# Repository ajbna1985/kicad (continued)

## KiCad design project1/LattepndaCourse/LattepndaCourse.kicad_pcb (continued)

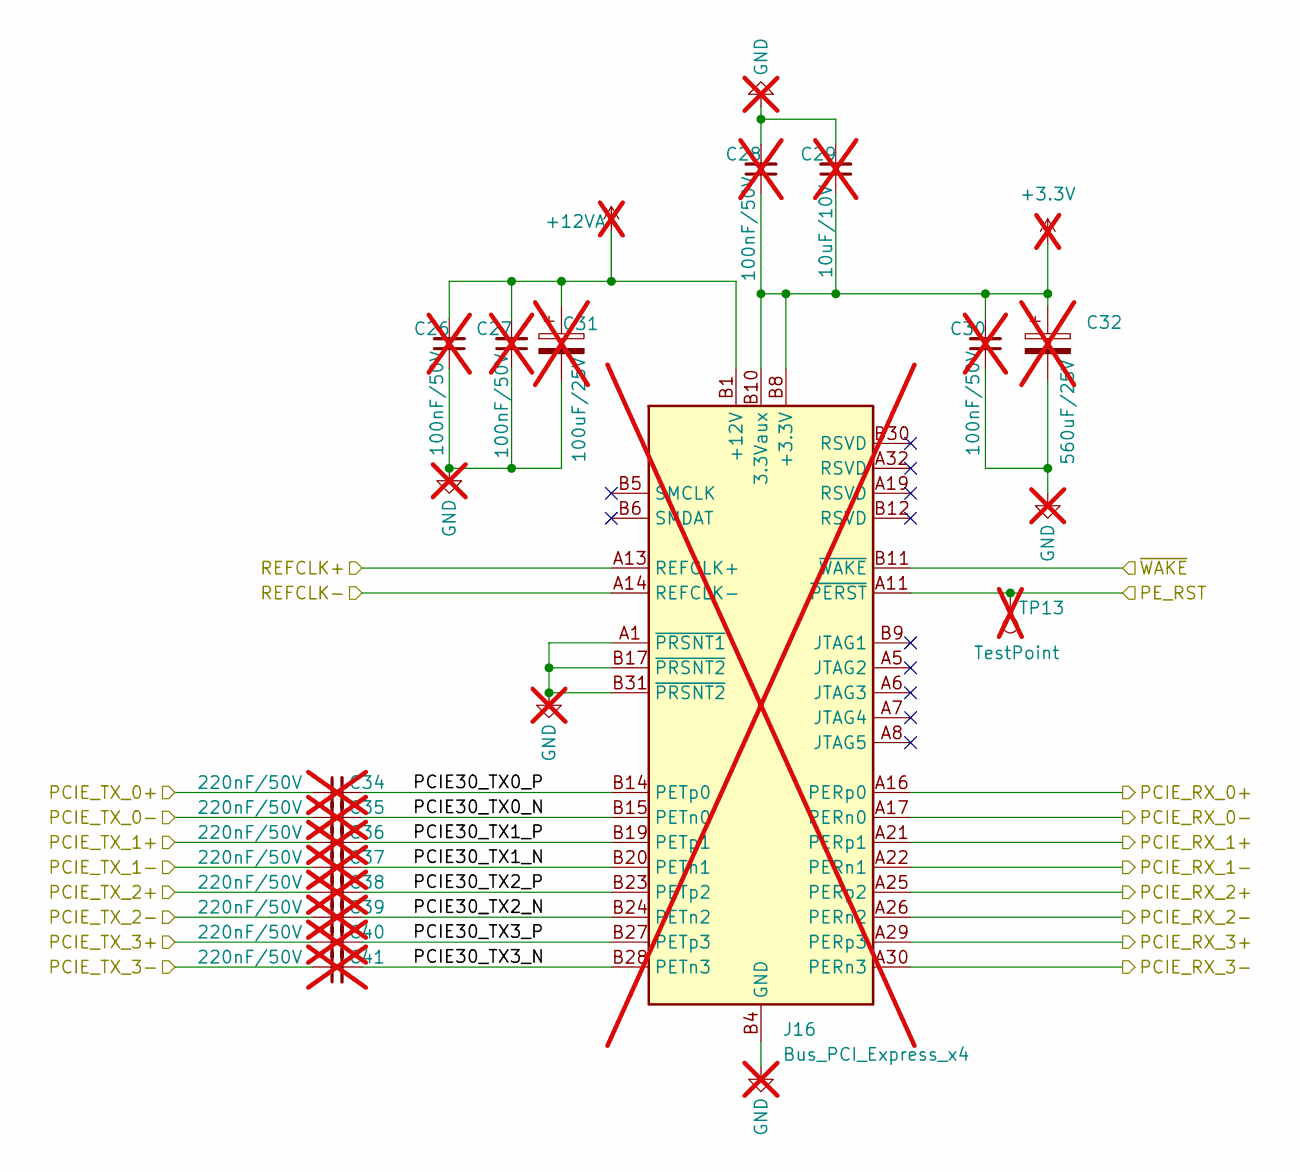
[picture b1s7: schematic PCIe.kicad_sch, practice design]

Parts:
C26, C27, C28, C30: 100nF/50V; C_0603_1608Metric; not fitted
C29: 10uF/10V; C_0603_1608Metric; not fitted
C31: 100uF/25V; CP_Elec_6.3x7.7; not fitted
C32: 560uF/25V; CP_Elec_6.3x7.7; not fitted
C34, C35, C36, C37, C38, C39, C40, C41: 220nF/50V; C_0402_1005Metric; not fitted
J16: Bus_PCI_Express_x4; PCIe_x4_Gen3Slot_Connectors; not fitted
TP13: TestPoint; TestPoint_Pad_D1.5mm; not fitted

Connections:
+3.3V: C28.1, C29.1, C30.2, C32.1, J16.A9 (+3.3V), J16.A10 (+3.3V), J16.B8 (+3.3V), J16.B10 (3.3Vaux); also elsewhere on the board
+5V: C26.1, C27.1, C28.2, C29.2, C30.1, C31.2, C32.2, J16.A1 (~PRSNT1), J16.A4 (GND), J16.A12 (GND), J16.A15 (GND), J16.A18 (GND), J16.A20 (GND), J16.A23 (GND), J16.A24 (GND), J16.A27 (GND), J16.A28 (GND), J16.A31 (GND), J16.B4 (GND), J16.B7 (GND), J16.B13 (GND), J16.B16 (GND), J16.B17 (~PRSNT2), J16.B18 (GND), J16.B21 (GND), J16.B22 (GND), J16.B25 (GND), J16.B26 (GND), J16.B29 (GND), J16.B31 (~PRSNT2), J16.B32 (GND); also elsewhere on the board
+12VA: C26.2, C27.2, C31.1, J16.A2 (+12V), J16.A3 (+12V), J16.B1 (+12V), J16.B2 (+12V), J16.B3 (+12V)
/LaPanda Module/HSIO_8_RX+: C34.1; also elsewhere on the board
/LaPanda Module/HSIO_8_RX-: C35.1; also elsewhere on the board
/LaPanda Module/HSIO_8_TX+: J16.A16 (PERp0); also elsewhere on the board
/LaPanda Module/HSIO_8_TX-: J16.A17 (PERn0); also elsewhere on the board
/LaPanda Module/HSIO_9_RX+: C36.1; also elsewhere on the board
/LaPanda Module/HSIO_9_RX-: C37.1; also elsewhere on the board
/LaPanda Module/HSIO_9_TX+: J16.A21 (PERp1); also elsewhere on the board
/LaPanda Module/HSIO_9_TX-: J16.A22 (PERn1); also elsewhere on the board
/LaPanda Module/HSIO_10_RX+: J16.A25 (PERp2); also elsewhere on the board
/LaPanda Module/HSIO_10_RX-: J16.A26 (PERn2); also elsewhere on the board
/LaPanda Module/HSIO_10_TX+: C38.1; also elsewhere on the board
/LaPanda Module/HSIO_10_TX-: C39.1; also elsewhere on the board
/LaPanda Module/HSIO_11_RX+: J16.A29 (PERp3); also elsewhere on the board
/LaPanda Module/HSIO_11_RX-: J16.A30 (PERn3); also elsewhere on the board
/LaPanda Module/HSIO_11_TX+: C40.1; also elsewhere on the board
/LaPanda Module/HSIO_11_TX-: C41.1; also elsewhere on the board
/LaPanda Module/REFCLK2+: J16.A13 (REFCLK+); also elsewhere on the board
/LaPanda Module/REFCLK2-: J16.A14 (REFCLK-); also elsewhere on the board
/PCIe/PCIE30_TX0_N: C35.2, J16.B15 (PETn0)
/PCIe/PCIE30_TX0_P: C34.2, J16.B14 (PETp0)
/PCIe/PCIE30_TX1_N: C37.2, J16.B20 (PETn1)
/PCIe/PCIE30_TX1_P: C36.2, J16.B19 (PETp1)
/PCIe/PCIE30_TX2_N: C39.2, J16.B24 (PETn2)
/PCIe/PCIE30_TX2_P: C38.2, J16.B23 (PETp2)
/PCIe/PCIE30_TX3_N: C41.2, J16.B28 (PETn3)
/PCIe/PCIE30_TX3_P: C40.2, J16.B27 (PETp3)
/~PLTRST: J16.A11 (~PERST), TP13.1 (1_1); also elsewhere on the board
/~WAKE: J16.B11 (~WAKE); also elsewhere on the board

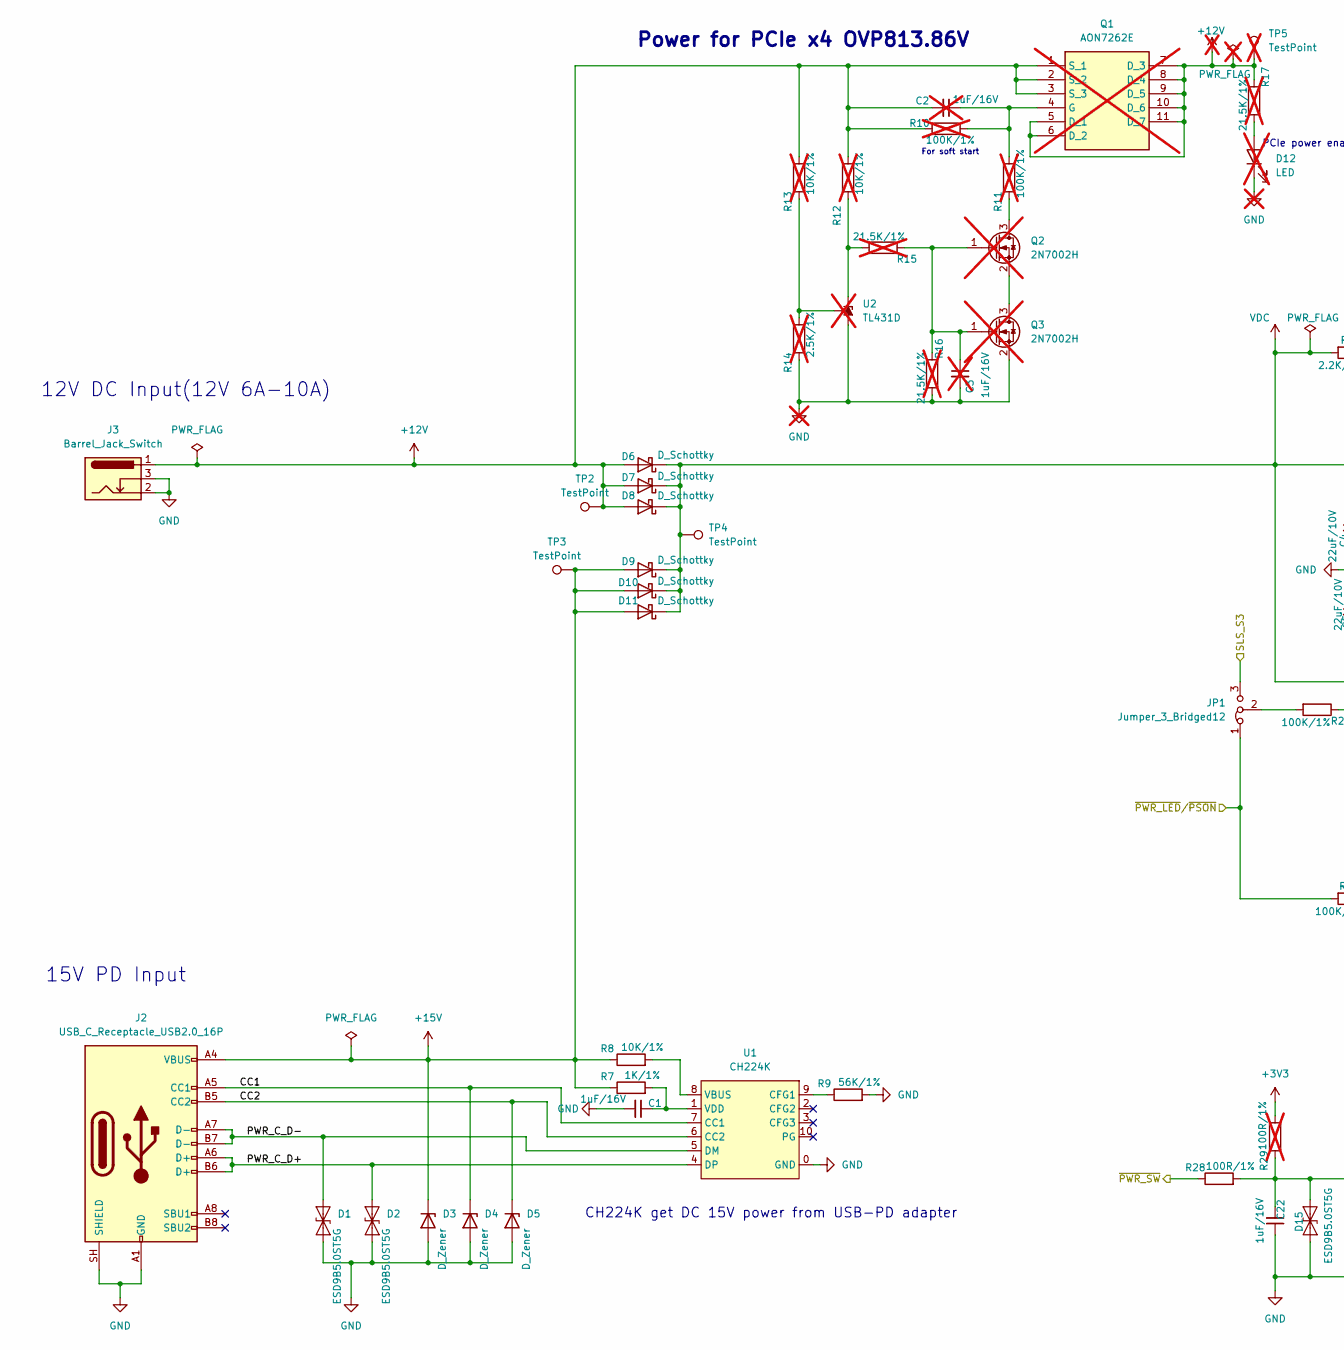
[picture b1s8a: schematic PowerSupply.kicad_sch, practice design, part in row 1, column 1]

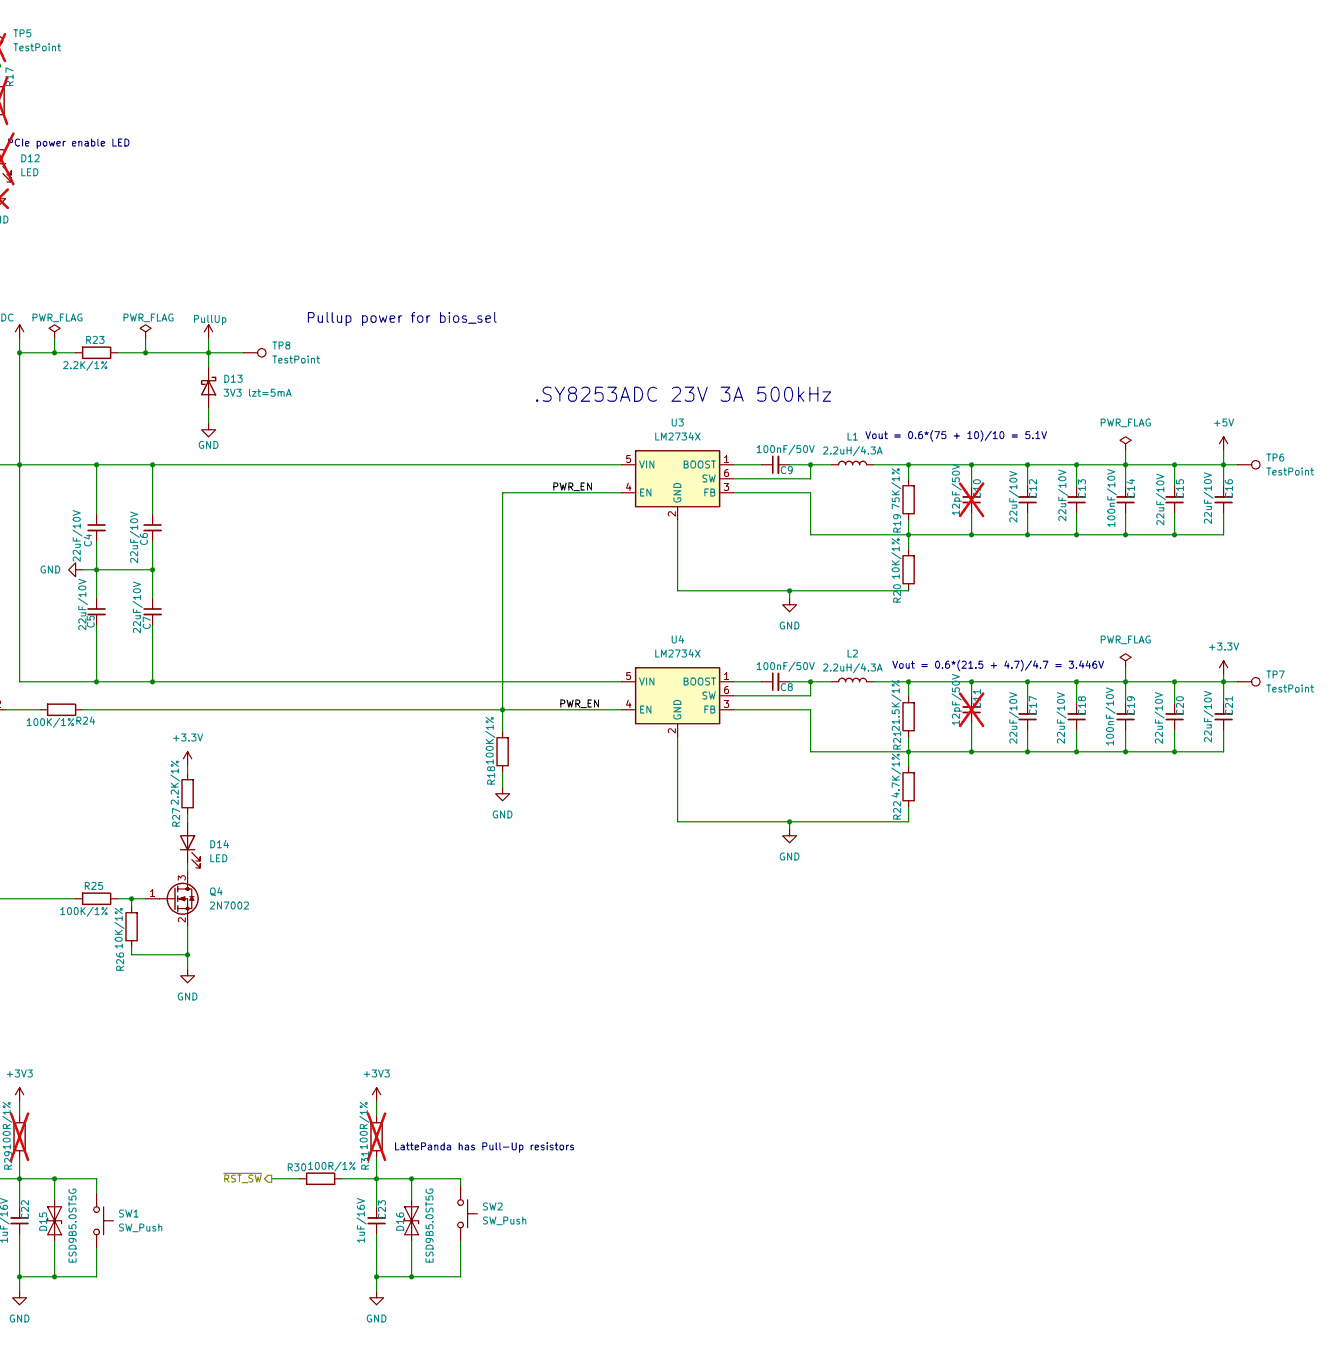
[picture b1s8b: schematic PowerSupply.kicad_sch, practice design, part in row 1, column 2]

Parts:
C1, C22, C23: 1uF/16V; C_0402_1005Metric
C2, C3: 1uF/16V; C_0402_1005Metric; not fitted
C4, C5, C6, C7, C12, C13, C15, C16, C17, C18, C20, C21: 22uF/10V; C_0603_1608Metric
C8, C9: 100nF/50V; C_0603_1608Metric
C10, C11: 12pF/50V; C_0603_1608Metric; not fitted
C14, C19: 100nF/10V; C_0603_1608Metric
D1, D2, D15, D16: ESD9B5.0ST5G; D_0402_1005Metric
D3, D4, D5: D_Zener; D_0402_1005Metric
D6, D7, D8, D9, D10, D11: D_Schottky; D_SMA
D12: LED; LED_0603_1608Metric; not fitted
D13: 3V3 lzt=5mA; D_SOD-323
D14: LED; LED_0603_1608Metric
J2: USB_C_Receptacle_USB2.0_16P; USB_C_Receptacle_G-Switch_GT-USB-7010ASV
J3: Barrel_Jack_Switch; DC_Jack_DC007B_30V_10A
JP1: Jumper_3_Bridged12; PinHeader_1x03_P2.54mm_Vertical
L1, L2: 2.2uH/4.3A; L_Sunlord_SWPA4020S
Q1: AON7262E; MOSFET_PDFN8_3.3x3.3; not fitted
Q2, Q3: 2N7002H; SOT-23; not fitted
Q4: 2N7002; SOT-23
R7: 1K/1%; R_0402_1005Metric
R8, R20, R26: 10K/1%; R_0402_1005Metric
R9: 56K/1%; R_0402_1005Metric
R10, R11: 100K/1%; R_0402_1005Metric; not fitted
R12, R13: 10K/1%; R_0402_1005Metric; not fitted
R14: 2.5K/1%; R_0402_1005Metric; not fitted
R15, R16, R17: 21.5K/1%; R_0402_1005Metric; not fitted
R18, R24, R25: 100K/1%; R_0402_1005Metric
R19: 75K/1%; R_0402_1005Metric
R21: 21.5K/1%; R_0402_1005Metric
R22: 4.7K/1%; R_0402_1005Metric
R23, R27: 2.2K/1%; R_0402_1005Metric
R28, R30: 100R/1%; R_0402_1005Metric
R29, R31: 100R/1%; R_0402_1005Metric; not fitted
SW1, SW2: SW_Push; SW_Push_6x6x6
TP2, TP3, TP4, TP6, TP7, TP8: TestPoint; TestPoint_Pad_D1.5mm
TP5: TestPoint; TestPoint_Pad_D1.5mm; not fitted
U1: USB PD等快充协议受电芯片-CH224K-ESSOP10; ESSOP-10-1EP_3.9x5mm_P1.0mm_EP3.2x2.3
U2: TL431D; SOT-23; not fitted
U3, U4: LM2734X; TSOT-23-6

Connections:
+3.3V: C11.2, C17.2, C18.2, C19.2, C20.2, C21.2, L2.2, R21.2, R27.2, TP7.1 (1_1); also elsewhere on the board
+3V3: R29.2, R31.2; also elsewhere on the board
+5V: C1.2, C3.2, C4.2, C5.1, C6.2, C7.1, C10.2, C12.2, C13.2, C14.2, C15.2, C16.2, C22.1, C23.1, D1.1 (A1), D2.1 (A1), D3.2 (A), D4.2 (A), D5.2 (A), D12.1 (K), D13.2 (A), D15.2 (A2), D16.2 (A2), J2.A1 (GND), J2.A12 (GND), J2.B1 (GND), J2.B12 (GND), J2.SH (SHIELD), J3.2, J3.3, L1.2, Q3.2 (S), Q4.2 (S), R9.2, R14.1, R16.2, R18.1, R19.2, R20.1, R22.1, R26.1, SW1.2, SW2.2, TP6.1 (1_1), U1.0 (GND), U2.2 (A), U2.3 (A), U2.6 (A), U2.7 (A), U3.2 (GND), U4.2 (GND); also elsewhere on the board
+12V: C2.2, D6.2 (A), D7.2 (A), D8.2 (A), J3.1, Q1.1 (S_1), Q1.2 (S_2), Q1.3 (S_3), Q1.5 (D_1), Q1.6 (D_2), Q1.7 (D_3), Q1.8 (D_4), Q1.9 (D_5), Q1.10 (D_6), Q1.11 (D_7), R10.1, R12.2, R13.2, R17.1, TP2.1 (1_1), TP5.1 (1_1); also elsewhere on the board
+15V: D3.1 (K), D9.2 (A), D10.2 (A), D11.2 (A), J2.A4 (VBUS), J2.A9 (VBUS), J2.B4 (VBUS), J2.B9 (VBUS), R7.1, R8.1, TP3.1 (1_1)
/LaPanda Module/SLS_S3: JP1.3 (B); also elsewhere on the board
/LaPanda Module/~RST_SW: R30.1; also elsewhere on the board
/PowerSupply/CC1: D4.1 (K), J2.A5 (CC1), U1.7 (CC1)
/PowerSupply/CC2: D5.1 (K), J2.B5 (CC2), U1.6 (CC2)
/PowerSupply/PWR_C_D+: D2.2 (A2), J2.A6 (D+), J2.B6 (D+), U1.4 (DP)
/PowerSupply/PWR_C_D-: D1.2 (A2), J2.A7 (D-), J2.B7 (D-), U1.5 (DM)
/PowerSupply/PWR_EN: R18.2, R24.1, U3.4 (EN), U4.4 (EN)
/~PWR_LED/~PSON: JP1.1 (A), R25.2; also elsewhere on the board
/~PWR_SW: R28.1; also elsewhere on the board
unnamed: D12.2 (A), R17.2
unnamed: D14.2 (A), R27.1
unnamed: D14.1 (K), Q4.3 (D)
unnamed: C22.2, D15.1 (A1), R28.2, R29.1, SW1.1
unnamed: C23.2, D16.1 (A1), R30.2, R31.1, SW2.1
unnamed: JP1.2 (C), R24.2
unnamed: C2.1, Q1.4 (G), R10.2, R11.2
unnamed: Q2.3 (D), R11.1
unnamed: C3.1, Q2.1 (G), Q3.1 (G), R15.1, R16.1
unnamed: Q2.2 (S), Q3.3 (D)
unnamed: Q4.1 (G), R25.1, R26.2
unnamed: R9.1, U1.9 (CFG1)
unnamed: R8.2, U1.8 (VBUS)
unnamed: C1.1, R7.2, U1.1 (VDD)
unnamed: R12.1, R15.2, U2.1 (K)
unnamed: R13.1, R14.2, U2.8 (REF)
unnamed: C9.1, U3.1 (BOOST)
unnamed: C10.1, C12.1, C13.1, C14.1, C15.1, C16.1, R19.1, R20.2, U3.3 (FB)
unnamed: C9.2, L1.1, U3.6 (SW)
unnamed: C8.1, U4.1 (BOOST)
unnamed: C11.1, C17.1, C18.1, C19.1, C20.1, C21.1, R21.1, R22.2, U4.3 (FB)
unnamed: C8.2, L2.1, U4.6 (SW)
PullUp: D13.1 (K), R23.1, TP8.1 (1_1); also elsewhere on the board
VDC: C4.1, C5.2, C6.1, C7.2, D6.1 (K), D7.1 (K), D8.1 (K), D9.1 (K), D10.1 (K), D11.1 (K), R23.2, TP4.1 (1_1), U3.5 (VIN), U4.5 (VIN); also elsewhere on the board

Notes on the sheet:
CH224K get DC 15V power from USB-PD adapter
For soft start
15V PD Input
Vout = 0.6*(75 + 10)/10 = 5.1V
Power for PCIe x4 OVP813.86V
PCIe power enable LED
Vout = 0.6*(21.5 + 4.7)/4.7 = 3.446V
LattePanda has Pull-Up resistors
.SY8253ADC 23V 3A 500kHz
Pullup power for bios_sel
12V DC Input(12V 6A-10A)

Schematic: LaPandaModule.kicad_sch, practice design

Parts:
A1: LattePanda_Mu; LattePanda_Module_H8.0mm_Horizontal
BT1: Battery_Cell; Battery_Holder_CR1220_S8411-45R
H7, H8: MountingHole_Pad; MountingHole_3mm_M2_Pad_TopOnly
J1: Conn_01x03_Pin; PinHeader_1x03_P2.54mm_Vertical
R1, R2, R3: 10K/1%; R_0402_1005Metric
R4, R5: 100K/1%; R_0402_1005Metric
R6: 1K/1%; R_0402_1005Metric
TP1: TestPoint; TestPoint_Pad_D1.5mm

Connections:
+5V: A1.11 (GND), A1.14 (GND), A1.17 (GND), A1.20 (GND), A1.23 (GND), A1.26 (GND), A1.29 (GND), A1.32 (GND), A1.35 (GND), A1.38 (GND), A1.41 (GND), A1.44 (GND), A1.47 (GND), A1.50 (GND), A1.53 (GND), A1.56 (GND), A1.59 (GND), A1.62 (GND), A1.65 (GND), A1.68 (GND), A1.71 (GND), A1.74 (GND), A1.77 (GND), A1.80 (GND), A1.83 (GND), A1.86 (GND), A1.89 (GND), A1.92 (GND), A1.95 (GND), A1.98 (GND), A1.101 (GND), A1.107 (GND), A1.110 (GND), A1.113 (GND), A1.116 (GND), A1.135 (GND), A1.136 (GND), A1.151 (GND), A1.158 (GND), A1.167 (GND), A1.170 (GND), A1.181 (GND), A1.182 (GND), A1.188 (GND), A1.189 (GND), A1.194 (GND), A1.195 (GND), A1.200 (GND), A1.201 (GND), A1.206 (GND), A1.207 (GND), A1.212 (GND), A1.213 (GND), A1.218 (GND), A1.219 (GND), A1.224 (GND), A1.225 (GND), A1.230 (GND), A1.231 (GND), A1.236 (GND), A1.237 (GND), A1.242 (GND), A1.243 (GND), A1.248 (GND), A1.249 (GND), A1.MP (Mountinge_Pads), BT1.2 (-), H7.1 (1_1), H8.1 (1_1), J1.3, R2.1, R3.1, R4.2, R5.2; also elsewhere on the board
+BATT: A1.115 (VBAT), R6.2
/Fan/FAN_1_PWM: A1.2 (FAN1_PWM); also elsewhere on the board
/Fan/FAN_1_TAC: A1.4 (FAN1_TAC); also elsewhere on the board
/Fan/FAN_2_PWM: A1.6 (FAN2_PWM); also elsewhere on the board
/Fan/FAN_2_TAC: A1.8 (FAN2_TAC); also elsewhere on the board
/Fan/TEMP: A1.9 (TSENSE); also elsewhere on the board
/GPIO/GPP_D0: A1.128 (GPP_D0); also elsewhere on the board
/GPIO/GPP_D1: A1.130 (GPP_D1); also elsewhere on the board
/GPIO/GPP_D2: A1.132 (GPP_D2); also elsewhere on the board
/GPIO/GPP_D3: A1.134 (GPP_D3); also elsewhere on the board
/GPIO/I2C2_SCL: A1.154 (I2C2_SCL); also elsewhere on the board
/GPIO/I2C2_SDA: A1.156 (I2C2_SDA); also elsewhere on the board
/GPIO/I2C3_SCL: A1.150 (I2C3_SCL); also elsewhere on the board
/GPIO/I2C3_SDA: A1.152 (I2C3_SDA); also elsewhere on the board
/GPIO/I2C4_SCL: A1.146 (I2C4_SCL); also elsewhere on the board
/GPIO/I2C4_SDA: A1.148 (I2C4_SDA); also elsewhere on the board
/GPIO/I2C5_SCL: A1.142 (I2C5_SCL); also elsewhere on the board
/GPIO/I2C5_SDA: A1.144 (I2C5_SDA); also elsewhere on the board
/GPIO/SOC_UART0_RX: A1.137 (UART0_RXD); also elsewhere on the board
/GPIO/SOC_UART0_TX: A1.139 (UART0_TXD); also elsewhere on the board
/GPIO/SOC_UART1_RX: A1.141 (UART1_RXD); also elsewhere on the board
/GPIO/SOC_UART1_TX: A1.143 (UART1_TXD); also elsewhere on the board
/GPIO/SOC_UART2_RX: A1.140 (UART2_RXD); also elsewhere on the board
/GPIO/SOC_UART2_TX: A1.138 (UART2_TXD); also elsewhere on the board
/GigbitEthernet/GbE_PCIe_CLK+: A1.94 (REFCLK4+); also elsewhere on the board
/GigbitEthernet/GbE_PCIe_CLK-: A1.96 (REFCLK4-); also elsewhere on the board
/GigbitEthernet/GbE_PCIe_RX+: A1.64 (HSIO6_RX+); also elsewhere on the board
/GigbitEthernet/GbE_PCIe_RX-: A1.66 (HSIO6_RX-); also elsewhere on the board
/GigbitEthernet/GbE_PCIe_TX+: A1.61 (HSIO6_TX+); also elsewhere on the board
/GigbitEthernet/GbE_PCIe_TX-: A1.63 (HSIO6_TX-); also elsewhere on the board
/HDMI/DDI_B_DDC_SCL: A1.171 (DDIB_DDC_SCL); also elsewhere on the board
/HDMI/DDI_B_DDC_SDA: A1.169 (DDIB_DDC_SDA); also elsewhere on the board
/HDMI/DDI_B_HPD: A1.183 (DDIB_HPD); also elsewhere on the board
/HDMI/DDI_B_TX0+: A1.217 (DDIB_TX0+); also elsewhere on the board
/HDMI/DDI_B_TX0-: A1.215 (DDIB_TX0-); also elsewhere on the board
/HDMI/DDI_B_TX1+: A1.211 (DDIB_TX1+); also elsewhere on the board
/HDMI/DDI_B_TX1-: A1.209 (DDIB_TX1-); also elsewhere on the board
/HDMI/DDI_B_TX2+: A1.205 (DDIB_TX2+); also elsewhere on the board
/HDMI/DDI_B_TX2-: A1.203 (DDIB_TX2-); also elsewhere on the board
/HDMI/DDI_B_TX3+: A1.199 (DDIB_TX3+); also elsewhere on the board
/HDMI/DDI_B_TX3-: A1.197 (DDIB_TX3-); also elsewhere on the board
/LaPanda Module/HSIO_0_RX+: A1.16 (HSIO0_RX+); also elsewhere on the board
/LaPanda Module/HSIO_0_RX-: A1.18 (HSIO0_RX-); also elsewhere on the board
/LaPanda Module/HSIO_1_TX+: A1.19 (HSIO1_TX+); also elsewhere on the board
/LaPanda Module/HSIO_1_TX-: A1.21 (HSIO1_TX-); also elsewhere on the board
/LaPanda Module/HSIO_2_RX+: A1.28 (HSIO2_RX+); also elsewhere on the board
/LaPanda Module/HSIO_2_RX-: A1.30 (HSIO2_RX-); also elsewhere on the board
/LaPanda Module/HSIO_2_TX+: A1.25 (HSIO2_TX+); also elsewhere on the board
/LaPanda Module/HSIO_2_TX-: A1.27 (HSIO2_TX-); also elsewhere on the board
/LaPanda Module/HSIO_3_RX+: A1.34 (HSIO3_RX+); also elsewhere on the board
/LaPanda Module/HSIO_3_RX-: A1.36 (HSIO3_RX-); also elsewhere on the board
/LaPanda Module/HSIO_3_TX+: A1.31 (HSIO3_TX+); also elsewhere on the board
/LaPanda Module/HSIO_3_TX-: A1.33 (HSIO3_TX-); also elsewhere on the board
/LaPanda Module/HSIO_8_RX+: A1.40 (HSIO8_RX+); also elsewhere on the board
/LaPanda Module/HSIO_8_RX-: A1.42 (HSIO8_RX-); also elsewhere on the board
/LaPanda Module/HSIO_8_TX+: A1.37 (HSIO8_TX+); also elsewhere on the board
/LaPanda Module/HSIO_8_TX-: A1.39 (HSIO8_TX-); also elsewhere on the board
/LaPanda Module/HSIO_9_RX+: A1.46 (HSIO9_RX+); also elsewhere on the board
/LaPanda Module/HSIO_9_RX-: A1.48 (HSIO9_RX-); also elsewhere on the board
/LaPanda Module/HSIO_9_TX+: A1.43 (HSIO9_TX+); also elsewhere on the board
/LaPanda Module/HSIO_9_TX-: A1.45 (HSIO9_TX-); also elsewhere on the board
/LaPanda Module/HSIO_10_RX+: A1.52 (HSIO10_RX+); also elsewhere on the board
/LaPanda Module/HSIO_10_RX-: A1.54 (HSIO10_RX-); also elsewhere on the board
/LaPanda Module/HSIO_10_TX+: A1.49 (HSIO10_TX+); also elsewhere on the board
/LaPanda Module/HSIO_10_TX-: A1.51 (HSIO10_TX-); also elsewhere on the board
/LaPanda Module/HSIO_11_RX+: A1.58 (HSIO11_RX+); also elsewhere on the board
/LaPanda Module/HSIO_11_RX-: A1.60 (HSIO11_RX-); also elsewhere on the board
/LaPanda Module/HSIO_11_TX+: A1.55 (HSIO11_TX+); also elsewhere on the board
/LaPanda Module/HSIO_11_TX-: A1.57 (HSIO11_TX-); also elsewhere on the board
/LaPanda Module/REFCLK0+: A1.85 (REFCLK0+); also elsewhere on the board
/LaPanda Module/REFCLK0-: A1.87 (REFCLK0-); also elsewhere on the board
/LaPanda Module/REFCLK2+: A1.97 (REFCLK2+); also elsewhere on the board
/LaPanda Module/REFCLK2-: A1.99 (REFCLK2-); also elsewhere on the board
/LaPanda Module/REFCLK3+: A1.88 (REFCLK3+); also elsewhere on the board
/LaPanda Module/REFCLK3-: A1.90 (REFCLK3-); also elsewhere on the board
/LaPanda Module/SLS_S3: A1.7 (SLS_S3); also elsewhere on the board
/LaPanda Module/SUSCLK_WIFI: A1.131 (SUSCLK); also elsewhere on the board
/LaPanda Module/USB2_P7+: A1.76 (USB2_P7+); also elsewhere on the board
/LaPanda Module/USB2_P7-: A1.78 (USB2_P7-); also elsewhere on the board
/LaPanda Module/~RST_SW: A1.3 (~RSTBTN); also elsewhere on the board
/USB 2&3/CON_USB1_D_N: A1.109 (USB2_P5-); also elsewhere on the board
/USB 2&3/CON_USB1_D_P: A1.111 (USB2_P5+); also elsewhere on the board
/USB 2&3/CON_USB2_D_N: A1.79 (USB2_P3-); also elsewhere on the board
/USB 2&3/CON_USB2_D_P: A1.81 (USB2_P3+); also elsewhere on the board
/USB 2&3/CON_USB3_D_N: A1.73 (USB2_P2-); also elsewhere on the board
/USB 2&3/CON_USB3_D_P: A1.75 (USB2_P2+); also elsewhere on the board
/USB 2&3/CON_USB3_SSRX_N: A1.15 (HSIO0_TX-); also elsewhere on the board
/USB 2&3/CON_USB3_SSRX_P: A1.13 (HSIO0_TX+); also elsewhere on the board
/USB 2&3/CON_USB4_D_N: A1.67 (USB2_P1-); also elsewhere on the board
/USB 2&3/CON_USB4_D_P: A1.69 (USB2_P1+); also elsewhere on the board
/USB 2&3/CON_USB4_SSRX_N: A1.24 (HSIO1_RX-); also elsewhere on the board
/USB 2&3/CON_USB4_SSRX_P: A1.22 (HSIO1_RX+); also elsewhere on the board
/~PLTRST: A1.105 (~PLTRST); also elsewhere on the board
/~PWR_LED/~PSON: A1.5 (SLS_S0); also elsewhere on the board
/~PWR_SW: A1.1 (~PWRBTN); also elsewhere on the board
/~WAKE: A1.103 (~WAKE); also elsewhere on the board
unnamed: A1.12 (SIO_UART_RX), J1.2
unnamed: A1.10 (SIO_UART_TX), J1.1
unnamed: A1.187 (TCP0_HPD), R4.1
unnamed: A1.185 (TCP1_HPD), R5.1
unnamed: A1.133 (~BIOS_SEL), R1.1, TP1.1 (1_1)
unnamed: A1.100 (~CLKREQ3), R3.2
unnamed: A1.102 (~CLKREQ4), R2.2
unnamed: BT1.1 (+), R6.1
PullUp: R1.2; also elsewhere on the board
VDC: A1.250 (VIN), A1.251 (VIN), A1.252 (VIN), A1.253 (VIN), A1.254 (VIN), A1.255 (VIN), A1.256 (VIN), A1.257 (VIN), A1.258 (VIN), A1.259 (VIN), A1.260 (VIN); also elsewhere on the board

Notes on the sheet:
HSIO_2 used for M.2 M KEY
HSIO_8/9/10/11 used for PCIe x4
HSIO functions are defined by the BIOS source code connot be changed in BIOS settings
USB2 P1/P2 used for USB3.0
USB2 P3/P4 used for USB2.0
Before starting design, you should choose one of the available BIOS configuration on: https://github.com/LattePandaTeam/LattePanda-Mu or contact technical support for custom your BIOS
DDI B used for HDMI
Lite Carrier has no second BIOS ROM ~{BIOS_SEL} pull up to 3.3V to select ROM on LattePanda Mu
SPI is only used to connect to the BIOS and discrete TPM. Cannot be used as a general SPI interface.
The default funtions ared defined as follows: -HSIO0: USB3.2 10Gbps -HSIO1: USB3.2 10Gbps -HSIO2: PCIe 3.0 x1 -HSIO3: PCIe 3.0 x1 -HSIO8: PCIe 3.0 x4 (lane 0) -HSIO9: PCIe 3.0 x4 (lane 1) -HSIO10: PCIe 3.0 x4 (lane 2) -HSIO11: PCIe 3.0 x4 (lane 3) -HSIO6: PCIe 3.0 x1
HPD pin of unused DDI/TCP port needs to be pulled down
~{CLKREQ} is reserved for PCIe ASPM L1s Unless the device clearly support it, pull it down to enhance compatiblity
USB2_P6 is reserved for TypeC PD controller Do not use it as a normal USB
All I2C have integrated pull-up resistors. No need to add pull-up resistors
HSIO_6 used for GbE(PCIe x1)
Sleeping State Signal -SLS_SO: -S0 (Working): HIGH -S3 (Sleeping): LOW -S4 (Hibernation): LOW -S3 (Soft Off): LOW -SLS_SO: -S0 (Working): HIGH -S3 (Sleeping): LOW -S4 (Hibernation): LOW -S3 (Soft Off): LOW
HSIO_3 used for M.2 E KEY
Before starting design, you should choose one of the available BIOS configuration on: https://github.com/LattePandaTeam/LattePanda-Mu or contact technical support for custom your BIOS The defualt funtions are defined as follows: -DDIA: eDP 1.4b (the 40 pin connector on Mu) -DDIB: HDMI 2.0 -TCP0: HD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
HSIO_0/HSIO_1 used for USB3.0

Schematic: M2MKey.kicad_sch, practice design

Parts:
C72, C74, C79, C81: 100nF/50V; C_0603_1608Metric
C73, C75, C78, C80: 10uF/50V; C_0603_1608Metric
C76, C77, C82, C83: 220nF/50V; C_0603_1608Metric
D27: LED_G; LED_0603_1608Metric
H5, H6: MountingHole_Pad; MountingHole_3.2mm_M3_Pad_Via
J20: Bus_M.2_Socket_M; PCIe_M.2_Connectors_P=0.5mm_H=4.2mm_KeyM
J21: Bus_M.2_Socket_E; PCIe_M.2_Connectors_P=0.5mm_H=4.2mm_KeyE
R65, R68, R70, R71: 0R/1%; R_0402_1005Metric
R69: 0R/1%; R_0402_1005Metric; not fitted
R72, R73: 10K/1%; R_0402_1005Metric
TP14: TestPoint; TestPoint_Pad_D1.5mm

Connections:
+3V3: C72.1, C73.2, C74.2, C75.2, C78.2, C79.2, C80.2, C81.1, D27.2 (A), J20.2 (3.3V), J20.4 (3.3V), J20.12 (3.3V), J20.14 (3.3V), J20.16 (3.3V), J20.18 (3.3V), J20.70 (3.3V), J20.72 (3.3V), J20.74 (3.3V), J21.2 (3.3V), J21.4 (3.3V), J21.72 (3.3V), J21.74 (3.3V), R72.2, R73.2; also elsewhere on the board
+5V: C72.2, C73.1, C74.1, C75.1, C78.1, C79.1, C80.1, C81.2, H5.1 (1_1), H6.1 (1_1), J20.1 (GND), J20.3 (GND), J20.9 (GND), J20.15 (GND), J20.21 (GND), J20.27 (GND), J20.33 (GND), J20.39 (GND), J20.45 (GND), J20.51 (GND), J20.57 (GND), J20.71 (GND), J20.73 (GND), J20.75 (GND), J21.1 (GND), J21.7 (GND), J21.18 (GND), J21.33 (GND), J21.39 (GND), J21.45 (GND), J21.51 (GND), J21.57 (GND), J21.63 (GND), J21.69 (GND), J21.75 (GND), R65.1, R69.2, R70.1; also elsewhere on the board
/LaPanda Module/HSIO_2_RX+: J20.43 (PERp0/SATA-B-); also elsewhere on the board
/LaPanda Module/HSIO_2_RX-: J20.41 (PERn0/SATA-B+); also elsewhere on the board
/LaPanda Module/HSIO_2_TX+: C76.2; also elsewhere on the board
/LaPanda Module/HSIO_2_TX-: C77.2; also elsewhere on the board
/LaPanda Module/HSIO_3_RX+: J21.41 (PERp0); also elsewhere on the board
/LaPanda Module/HSIO_3_RX-: J21.43 (PERn0); also elsewhere on the board
/LaPanda Module/HSIO_3_TX+: C82.2; also elsewhere on the board
/LaPanda Module/HSIO_3_TX-: C83.2; also elsewhere on the board
/LaPanda Module/REFCLK0+: J20.53 (REFCLKn); also elsewhere on the board
/LaPanda Module/REFCLK0-: J20.55 (REFCLKp); also elsewhere on the board
/LaPanda Module/REFCLK3+: J21.47 (REFCLKp0); also elsewhere on the board
/LaPanda Module/REFCLK3-: J21.49 (REFCLKn0); also elsewhere on the board
/LaPanda Module/SUSCLK_WIFI: R68.2, R71.2; also elsewhere on the board
/LaPanda Module/USB2_P7+: J21.3 (USB_D+); also elsewhere on the board
/LaPanda Module/USB2_P7-: J21.5 (USB_D-); also elsewhere on the board
/M2 M Key/CON_PCIE_TX1+: C76.1, C82.1, J20.49 (PETp0/SATA-A+), J21.35 (PETp0)
/M2 M Key/CON_PCIE_TX1-: C77.1, C83.1, J20.47 (PETn0/SATA-A-), J21.37 (PETn0)
/M2 M Key/~CLKREQE: J21.53 (~CLKREQ0), R70.2
/M2 M Key/~CLKREQM: J20.52 (~CLKREQ), R65.2
/~PLTRST: J20.50 (~PERST), J21.52 (~PERST0); also elsewhere on the board
/~WAKE: J20.54 (~PEWAKE), J21.55 (~PEWAKE0); also elsewhere on the board
unnamed: D27.1 (K), J20.10 (DAS/~DSS/~LED1)
unnamed: J20.38 (DEVSLP), TP14.1 (1_1)
unnamed: J20.69 (PEDET), R69.1
unnamed: J20.68 (SUSCLK), R68.1
unnamed: J21.50 (SUSCLK), R71.1
unnamed: J21.56 (~W_DISABLE1), R73.1
unnamed: J21.54 (~W_DISABLE2), R72.1

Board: 4 copper layers, 270 parts (0 on the bottom side), 213 nets, no tracks yet.
